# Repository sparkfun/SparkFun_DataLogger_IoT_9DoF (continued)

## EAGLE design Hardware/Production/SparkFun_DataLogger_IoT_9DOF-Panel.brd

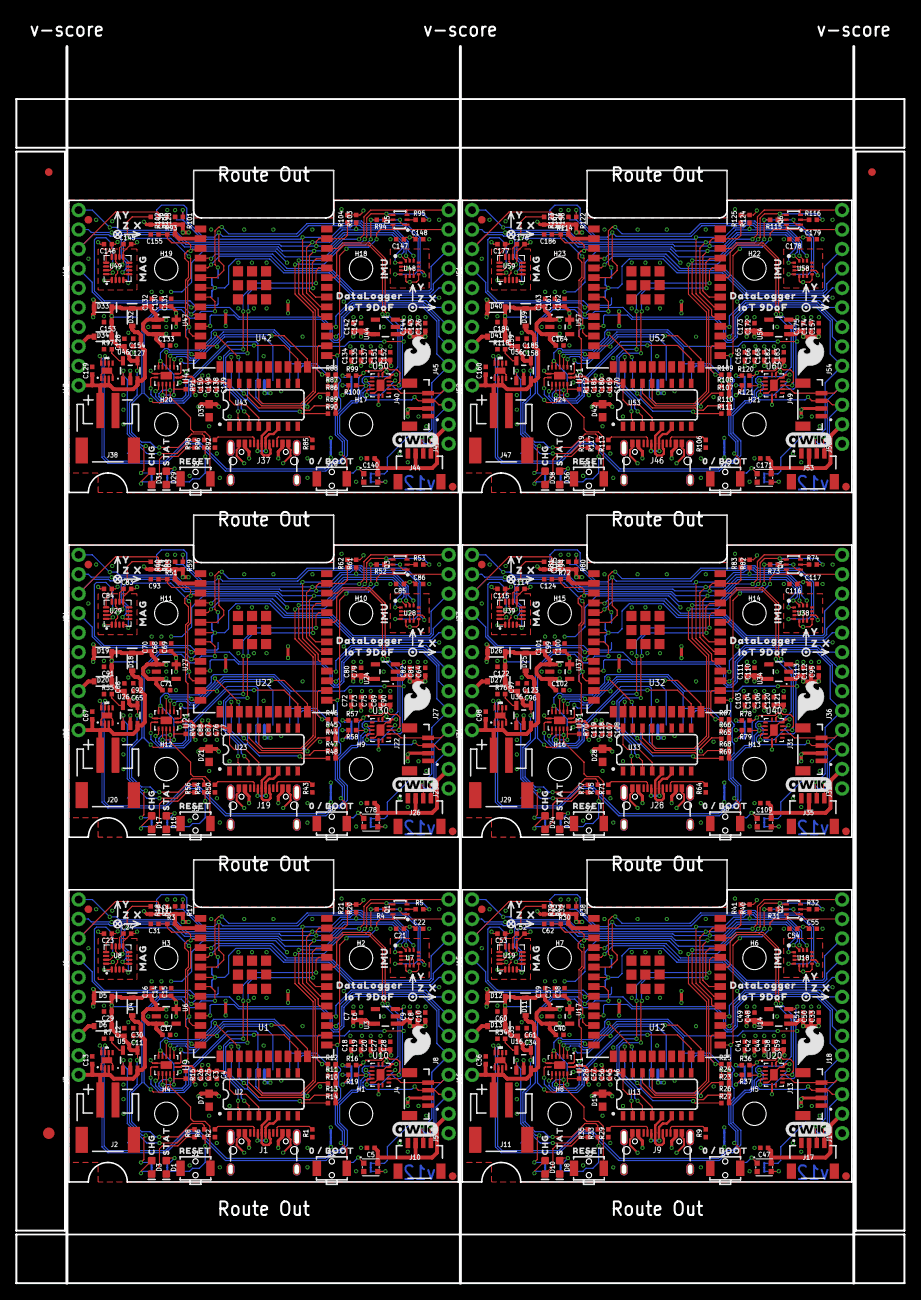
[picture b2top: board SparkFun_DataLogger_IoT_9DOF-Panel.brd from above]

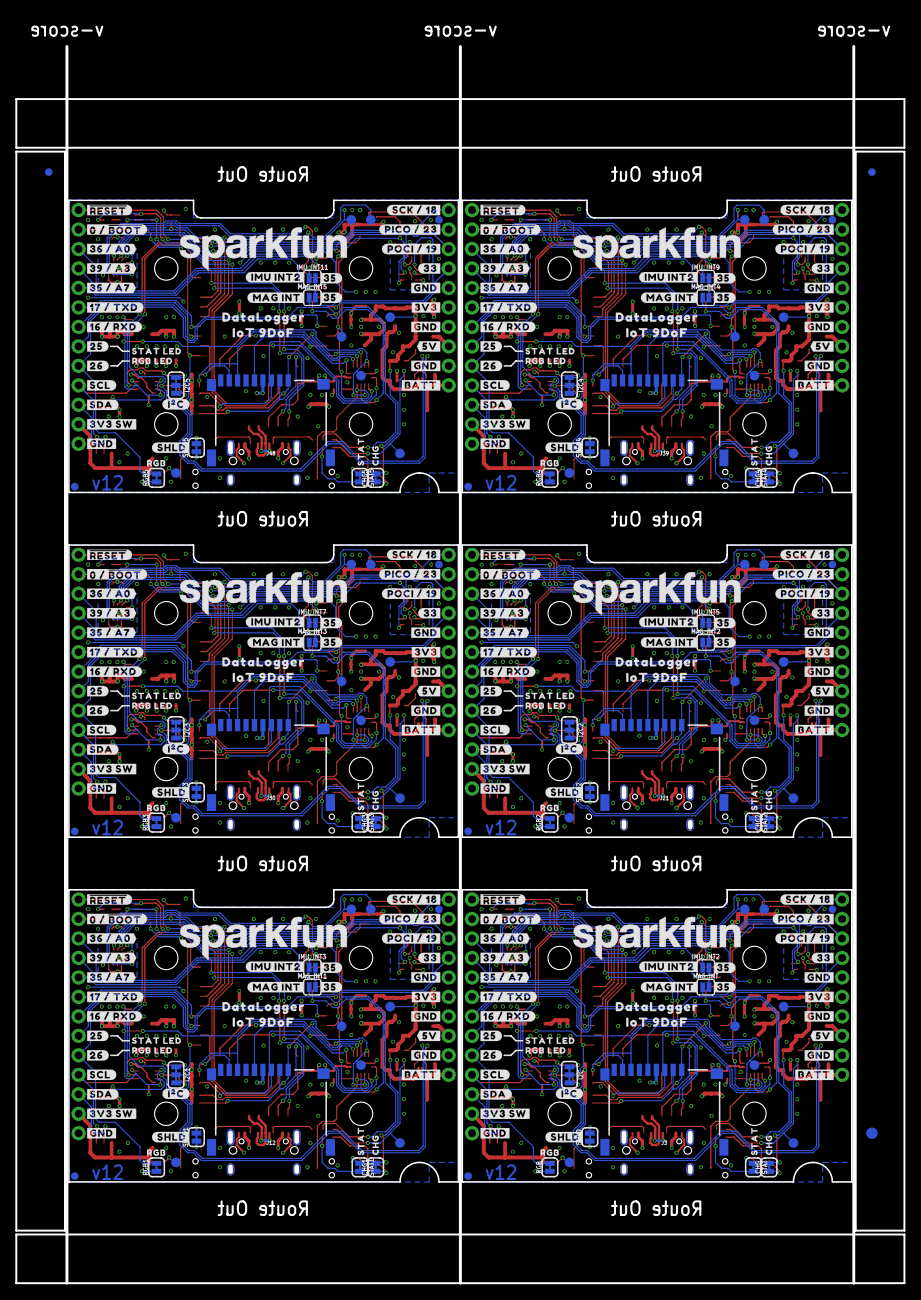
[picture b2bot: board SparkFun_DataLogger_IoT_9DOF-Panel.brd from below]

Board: 4 copper layers, 115.8 x 161.3 mm, 942 parts (327 on the bottom side), 372 nets.

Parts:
C1, C3, C5, C6, C8, C9, C10, C11, C12, C14, C16, C18, C20, C23, C25, C26, C27, C28, C29, C30, C32, C33, C34, C35, C37, C39, C41, C44, C45, C47, C48, C50, C51, C53, C56, C57, C58, C59, C60, C61, C63, C64, C65, C66, C68, C70, C72, C75, C76, C78, C79, C81, C82, C84, C87, C88, C89, C90, C91, C92, C94, C95, C96, C97, C99, C101, C103, C106, C107, C109, C110, C112, C113, C115, C118, C119, C120, C121, C122, C123, C125, C126, C127, C128, C130, C132, C134, C137, C138, C140, C141, C143, C144, C146, C149, C150, C151, C152, C153, C154, C156, C157, C158, C159, C161, C163, C165, C168, C169, C171, C172, C174, C175, C177, C180, C181, C182, C183, C184, C185: 2.2uF; 0402-TIGHT
C2, C7, C13, C15, C17, C19, C21, C22, C36, C38, C40, C42, C43, C49, C54, C55, C67, C69, C71, C73, C74, C80, C85, C86, C98, C100, C102, C104, C105, C111, C116, C117, C129, C131, C133, C135, C136, C142, C147, C148, C160, C162, C164, C166, C167, C173, C178, C179: 0.1uF; 0402-TIGHT
C4, C46, C77, C108, C139, C170: 10nF; 0402-TIGHT
C24, C52, C83, C114, C145, C176: 10uF; 0402-TIGHT
C31, C62, C93, C124, C155, C186: DNP; 0402-TIGHT_NO_CREAM
CHG, CHG1, CHG2, CHG3, CHG4, CHG5: JUMPER-SMT_2_NC_TRACE_SILK; SMT-JUMPER_2_NC_TRACE_SILK
D1, D8, D15, D22, D29, D36: BLUE; LED-0603
D2, D9, D16, D23, D30, D37: WS2812_2020; WS2812-2020
D3, D10, D17, D24, D31, D38: Yellow; LED-0603
D4, D5, D6, D11, D12, D13, D18, D19, D20, D25, D26, D27, D32, D33, D34, D39, D40, D41: 3A/10V/280mV; SOD-323
D7, D14, D21, D28, D35, D42: TVS; 0603
E$1, E$2, E$3, E$4: FIDUCIAL-1X2
E$5, E$6: FIDUCIAL-1.5X3
FD1, FD2, FD3, FD4, FD5, FD6, FD7, FD8, FD9, FD10, FD11, FD12, FD13, FD14, FD15, FD16, FD17, FD18, FD19, FD20, FD21, FD22, FD23, FD24: FIDUCIAL1X2; FIDUCIAL-1X2
H1, H2, H3, H4, H5, H6, H7, H8, H9, H10, H11, H12, H13, H14, H15, H16, H17, H18, H19, H20, H21, H22, H23, H24: STAND-OFFTIGHT; STAND-OFF-TIGHT
I2C, I2C1, I2C2, I2C3, I2C4, I2C5: JUMPER-SMT_3_2-NC_TRACE_SILK; SMT-JUMPER_3_2-NC_TRACE_SILK
IMU_!CS!, IMU_!CS!1, IMU_!CS!2, IMU_!CS!3, IMU_!CS!4, IMU_!CS!5: TEST-POINT3X5; PAD.03X.05
IMU_INT1, IMU_INT4, IMU_INT6, IMU_INT8, IMU_INT10, IMU_INT12: TEST-POINT3X5; PAD.03X.05
IMU_INT2, IMU_INT3, IMU_INT5, IMU_INT7, IMU_INT9, IMU_INT11: JUMPER-SMT_2_NO_SILK; SMT-JUMPER_2_NO_SILK
J1, J9, J19, J28, J37, J46: USB-C-16P_4LAYER-PADS
J2, J11, J20, J29, J38, J47: JST-2-SMD
J3, J12, J21, J30, J39, J48: MICRO-SD-PUSH-PUSH-EXT-PIN; MICROSD-EXTERNALPIN
J4, J13, J22, J31, J40, J49: Vertical Qwiic Connector; JST04_1MM_VERT
J5, J6, J14, J15, J23, J24, J32, J33, J41, J42, J50, J51: 1X04_NO_SILK
J7, J16, J25, J34, J43, J52: 1X06_NO_SILK
J8, J18, J27, J36, J45, J54: 1X09_NO_SILK
J10, J17, J26, J35, J44, J53: QWIIC_RIGHT_ANGLE; JST04_1MM_RA
LOGO1, LOGO3, LOGO7, LOGO10, LOGO13, LOGO16: QWIIC_LOGO_6MM; QWIIC_6MM
LOGO2, LOGO5, LOGO8, LOGO11, LOGO14, LOGO17: SFE_LOGO_NAME.2_INCH; SFE_LOGO_NAME_.2
LOGO4, LOGO6, LOGO9, LOGO12, LOGO15, LOGO18: SFE_LOGO_FLAME.2_INCH; SFE_LOGO_FLAME_.2
MAG_!CS!, MAG_!CS!1, MAG_!CS!2, MAG_!CS!3, MAG_!CS!4, MAG_!CS!5: TEST-POINT3X5; PAD.03X.05
MAG_INT, MAG_INT1, MAG_INT2, MAG_INT3, MAG_INT4, MAG_INT5: JUMPER-SMT_2_NO_SILK; SMT-JUMPER_2_NO_SILK
PWREN, PWREN1, PWREN2, PWREN3, PWREN4, PWREN5: TEST-POINT3X5; PAD.03X.05
Q1, Q2, Q3, Q4, Q5, Q6: SC70-6
R1, R2, R9, R29, R43, R50, R64, R71, R85, R92, R106, R113: 5.1k; 0402-TIGHT
R3, R4, R5, R10, R11, R12, R13, R14, R22, R23, R24, R25, R26, R27, R30, R31, R32, R42, R44, R45, R46, R47, R48, R51, R52, R53, R63, R65, R66, R67, R68, R69, R72, R73, R74, R84, R86, R87, R88, R89, R90, R93, R94, R95, R105, R107, R108, R109, R110, R111, R114, R115, R116, R126: 10k; 0402-TIGHT
R6, R8, R33, R35, R54, R56, R75, R77, R96, R98, R117, R119: 1k; 0402-TIGHT
R7, R34, R55, R76, R97, R118: 2.0K; 0402-TIGHT
R15, R17, R18, R20, R21, R28, R38, R39, R40, R41, R49, R59, R60, R61, R62, R70, R80, R81, R82, R83, R91, R101, R102, R103, R104, R112, R122, R123, R124, R125: 100k; 0402-TIGHT
R16, R19, R36, R37, R57, R58, R78, R79, R99, R100, R120, R121: 2.2k; 0402-TIGHT
RGB, RGB1, RGB2, RGB3, RGB4, RGB5: JUMPER-SMT_2_NC_TRACE_SILK; SMT-JUMPER_2_NC_TRACE_SILK
S1, S3, S5, S7, S9, S11: RESET; TACTILE_SWITCH_SMD_RIGHT_ANGLE
S2, S4, S6, S8, S10, S12: BOOT; TACTILE_SWITCH_SMD_RIGHT_ANGLE
SHLD, SHLD1, SHLD2, SHLD3, SHLD4, SHLD5: JUMPER-SMT_2_NC_TRACE_SILK; SMT-JUMPER_2_NC_TRACE_SILK
STAT, STAT1, STAT2, STAT3, STAT4, STAT5: JUMPER-SMT_2_NC_TRACE_SILK; SMT-JUMPER_2_NC_TRACE_SILK
TP1, TP2, TP3, TP4, TP5, TP6: TEST-POINT3X5; PAD.03X.05
U1, U12, U22, U32, U42, U52: ESP-WROOM-32E; ESP-WROOM-32D-NARROW
U2, U13, U23, U33, U43, U53: CH340C; SO016
U3, U6, U14, U17, U24, U27, U34, U37, U44, U47, U54, U57: XC6222B331MR-G; SOT23-5
U4, U15, U25, U35, U45, U55: MAX17048; DFN-8
U5, U16, U26, U36, U46, U56: MCP73831; SOT23-5
U7, U18, U28, U38, U48, U58: ISM330DHCX; LGA-14L
U8, U19, U29, U39, U49, U59: MMC5983MA_QFN16; LGA-16-3X3MM-4X4PINS
U9, U10, U11, U20, U21, U30, U31, U40, U41, U50, U51, U60: 74HC4066_QUAD_BILATERAL_SWITCH_QFN; 14-QFN
U$1, U$99, U$149, U$199, U$249, U$299: IOT_9DOF0
U$2, U$39, U$101, U$151, U$201, U$251: RESET0
U$3, U$6, U$52, U$55, U$102, U$105, U$152, U$155, U$202, U$205, U$252, U$255: STAT0
U$4, U$5, U$53, U$54, U$103, U$104, U$153, U$154, U$203, U$204, U$253, U$254: CHG0
U$7, U$95, U$145, U$195, U$245, U$295: 0_#_BOOT0
U$8, U$56, U$106, U$156, U$206, U$256: IMU0
U$9, U$57, U$107, U$157, U$207, U$257: MAG0
U$10, U$13, U$58, U$61, U$108, U$111, U$158, U$161, U$208, U$211, U$258, U$261: X0
U$11, U$14, U$59, U$62, U$109, U$112, U$159, U$162, U$209, U$212, U$259, U$262: Y0
U$12, U$15, U$60, U$63, U$110, U$113, U$160, U$163, U$210, U$213, U$260, U$263: Z0
U$16, U$64, U$114, U$164, U$214, U$264: ##RESET##0
U$17, U$65, U$115, U$165, U$215, U$265: #0_#_#BOOT##0
U$18, U$66, U$116, U$166, U$216, U$266: #36_#_A0#0
U$19, U$67, U$117, U$167, U$217, U$267: #39_#_A3#0
U$20, U$68, U$118, U$168, U$218, U$268: #35_#_A7#0
U$21, U$69, U$119, U$169, U$219, U$269: #17_#_TXD#0
U$22, U$70, U$120, U$170, U$220, U$270: #16_#_RXD#0
U$23, U$71, U$121, U$171, U$221, U$271: #25#0
U$24, U$72, U$122, U$172, U$222, U$272: #26#0
U$25, U$73, U$123, U$173, U$223, U$273: #SCL#0
U$26, U$74, U$124, U$174, U$224, U$274: #SDA#0
U$27, U$75, U$125, U$175, U$225, U$275: #3V3_SW#0
U$28, U$76, U$126, U$176, U$226, U$276: #GND#0
U$29, U$30, U$31, U$77, U$78, U$79, U$127, U$128, U$129, U$177, U$178, U$179, U$227, U$228, U$229, U$277, U$278, U$279: #GND#1
U$32, U$80, U$130, U$180, U$230, U$280: #BATT#0
U$33, U$81, U$131, U$181, U$231, U$281: #5V#0
U$34, U$82, U$132, U$182, U$232, U$282: #3V3#0
U$35, U$83, U$133, U$183, U$233, U$283: #33#0
U$36, U$84, U$134, U$184, U$234, U$284: #POCI_#_19#0
U$37, U$85, U$135, U$185, U$235, U$285: #PICO_#_23#0
U$38, U$86, U$136, U$186, U$236, U$286: #SCK_#_18#0
U$40, U$87, U$137, U$187, U$237, U$287: #IMU_INT2#0
U$41, U$88, U$138, U$188, U$238, U$288: #MAG_INT#0
U$42, U$43, U$89, U$90, U$139, U$140, U$189, U$190, U$239, U$240, U$289, U$290: #35#0
U$44, U$100, U$150, U$200, U$250, U$300: IOT_9DOF10
U$45, U$91, U$141, U$191, U$241, U$291: #SHLD#0
U$46, U$92, U$142, U$192, U$242, U$292: #I�C#0
U$47, U$93, U$143, U$193, U$243, U$293: STAT_LED0
U$48, U$94, U$144, U$194, U$244, U$294: RGB_LED0
U$49, U$96, U$146, U$196, U$246, U$296: RGB0
U$50, U$97, U$147, U$197, U$247, U$297: DATALOGGER0
U$51, U$98, U$148, U$198, U$248, U$298: DATALOGGER1
VIN, VIN1, VIN2, VIN3, VIN4, VIN5, VIN6, VIN7, VIN8, VIN9, VIN10, VIN11: TEST-POINT3X5; PAD.03X.05

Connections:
3.3V: C1.1, C2.1, C3.1, C4.1, C14.1, C15.1, C21.1, C22.1, C23.1, C25.1, C26.1, C27.1, C28.1, I2C.2, J7.5, R3.2, R17.2, R18.2, R20.2, R21.2, R22.2, U1.2, U2.4, U2.16, U6.5, U7.P5, U7.P8, U8.2, U8.13, U9.14, U10.14
3.3V1: C32.1, C37.1, C38.1, C43.1, C45.1, C46.1, C53.1, C54.1, C55.1, C56.1, C57.1, C58.1, C59.1, I2C1.2, J16.5, R30.2, R38.2, R39.2, R40.2, R41.2, R42.2, U11.14, U12.2, U13.4, U13.16, U17.5, U18.P5, U18.P8, U19.2, U19.13, U20.14
3.3V2: C63.1, C68.1, C69.1, C74.1, C76.1, C77.1, C84.1, C85.1, C86.1, C87.1, C88.1, C89.1, C90.1, I2C2.2, J25.5, R51.2, R59.2, R60.2, R61.2, R62.2, R63.2, U21.14, U22.2, U23.4, U23.16, U27.5, U28.P5, U28.P8, U29.2, U29.13, U30.14
3.3V3: C94.1, C99.1, C100.1, C105.1, C107.1, C108.1, C115.1, C116.1, C117.1, C118.1, C119.1, C120.1, C121.1, I2C3.2, J34.5, R72.2, R80.2, R81.2, R82.2, R83.2, R84.2, U31.14, U32.2, U33.4, U33.16, U37.5, U38.P5, U38.P8, U39.2, U39.13, U40.14
3.3V4: C125.1, C130.1, C131.1, C136.1, C138.1, C139.1, C146.1, C147.1, C148.1, C149.1, C150.1, C151.1, C152.1, I2C4.2, J43.5, R93.2, R101.2, R102.2, R103.2, R104.2, R105.2, U41.14, U42.2, U43.4, U43.16, U47.5, U48.P5, U48.P8, U49.2, U49.13, U50.14
3.3V5: C156.1, C161.1, C162.1, C167.1, C169.1, C170.1, C177.1, C178.1, C179.1, C180.1, C181.1, C182.1, C183.1, I2C5.2, J52.5, R114.2, R122.2, R123.2, R124.2, R125.2, R126.2, U51.14, U52.2, U53.4, U53.16, U57.5, U58.P5, U58.P8, U59.2, U59.13, U60.14
3.3V_SW: C5.1, C6.1, C7.1, C18.1, C19.1, C20.1, D2.VCC, J3.4, J4.2, J5.2, J10.2, R10.2, R11.2, R12.2, R13.2, R14.2, U3.5
3.3V_SW1: C41.1, C42.1, C44.1, C47.1, C48.1, C49.1, D9.VCC, J12.4, J13.2, J14.2, J17.2, R23.2, R24.2, R25.2, R26.2, R27.2, U14.5
3.3V_SW2: C72.1, C73.1, C75.1, C78.1, C79.1, C80.1, D16.VCC, J21.4, J22.2, J23.2, J26.2, R44.2, R45.2, R46.2, R47.2, R48.2, U24.5
3.3V_SW3: C103.1, C104.1, C106.1, C109.1, C110.1, C111.1, D23.VCC, J30.4, J31.2, J32.2, J35.2, R65.2, R66.2, R67.2, R68.2, R69.2, U34.5
3.3V_SW4: C134.1, C135.1, C137.1, C140.1, C141.1, C142.1, D30.VCC, J39.4, J40.2, J41.2, J44.2, R86.2, R87.2, R88.2, R89.2, R90.2, U44.5
3.3V_SW5: C165.1, C166.1, C168.1, C171.1, C172.1, C173.1, D37.VCC, J48.4, J49.2, J50.2, J53.2, R107.2, R108.2, R109.2, R110.2, R111.2, U54.5
5V: D6.A, J7.3
5V1: D13.A, J16.3
5V2: D20.A, J25.3
5V3: D27.A, J34.3
5V4: D34.A, J43.3
5V5: D41.A, J52.3
!RESET!: C31.1, J8.9, Q1.3, R3.1, S1.2, U1.3, U9.12
!RESET!1: C62.1, J18.9, Q2.3, R30.1, S3.2, U11.12, U12.3
!RESET!2: C93.1, J27.9, Q3.3, R51.1, S5.2, U21.12, U22.3
!RESET!3: C124.1, J36.9, Q4.3, R72.1, S7.2, U31.12, U32.3
!RESET!4: C155.1, J45.9, Q5.3, R93.1, S9.2, U41.12, U42.3
!RESET!5: C186.1, J54.9, Q6.3, R114.1, S11.2, U51.12, U52.3
CAP: C24.1, U8.10
CAP1: C52.1, U19.10
CAP2: C83.1, U29.10
CAP3: C114.1, U39.10
CAP4: C145.1, U49.10
CAP5: C176.1, U59.10
CH340-DTR: Q1.1, R4.2, U2.13
CH340-DTR1: Q2.1, R31.2, U13.13
CH340-DTR2: Q3.1, R52.2, U23.13
CH340-DTR3: Q4.1, R73.2, U33.13
CH340-DTR4: Q5.1, R94.2, U43.13
CH340-DTR5: Q6.1, R115.2, U53.13
CH340-RTS: Q1.4, R5.2, U2.14
CH340-RTS1: Q2.4, R32.2, U13.14
CH340-RTS2: Q3.4, R53.2, U23.14
CH340-RTS3: Q4.4, R74.2, U33.14
CH340-RTS4: Q5.4, R95.2, U43.14
CH340-RTS5: Q6.4, R116.2, U53.14
CH340-RX: U1.35, U2.3
CH340-RX1: U12.35, U13.3
CH340-RX2: U22.35, U23.3
CH340-RX3: U32.35, U33.3
CH340-RX4: U42.35, U43.3
CH340-RX5: U52.35, U53.3
CH340-TX: U1.34, U2.2
CH340-TX1: U12.34, U13.2
CH340-TX2: U22.34, U23.2
CH340-TX3: U32.34, U33.2
CH340-TX4: U42.34, U43.2
CH340-TX5: U52.34, U53.2
D+: J1.A6, J1.B6, U2.5
D+1: J9.A6, J9.B6, U13.5
D+2: J19.A6, J19.B6, U23.5
D+3: J28.A6, J28.B6, U33.5
D+4: J37.A6, J37.B6, U43.5
D+5: J46.A6, J46.B6, U53.5
D-: J1.A7, J1.B7, U2.6
D-1: J9.A7, J9.B7, U13.6
D-2: J19.A7, J19.B7, U23.6
D-3: J28.A7, J28.B7, U33.6
D-4: J37.A7, J37.B7, U43.6
D-5: J46.A7, J46.B7, U53.6
ESP0/!BOOT!: J8.8, Q1.6, S2.2, U1.25
ESP0/!BOOT!1: J18.8, Q2.6, S4.2, U12.25
ESP0/!BOOT!2: J27.8, Q3.6, S6.2, U22.25
ESP0/!BOOT!3: J36.8, Q4.6, S8.2, U32.25
ESP0/!BOOT!4: J45.8, Q5.6, S10.2, U42.25
ESP0/!BOOT!5: J54.8, Q6.6, S12.2, U52.25
ESP1: J15.1, U12.9
ESP2: J24.1, U22.9
ESP2/DAT0: U1.24, U9.1
ESP2/DAT1: U11.1, U12.24
ESP2/DAT2: U21.1, U22.24
ESP2/DAT3: U31.1, U32.24
ESP2/DAT4: U41.1, U42.24
ESP2/DAT5: U51.1, U52.24
ESP3: J33.1, U32.9
ESP4: J42.1, U42.9
ESP4/DAT1: J3.8, R12.1, U1.26
ESP4/DAT2: J12.8, R25.1, U12.26
ESP4/DAT3: J21.8, R46.1, U22.26
ESP4/DAT4: J30.8, R67.1, U32.26
ESP4/DAT5: J39.8, R88.1, U42.26
ESP4/DAT6: J48.8, R109.1, U52.26
ESP5: J51.1, U52.9
ESP5/!IMU_CS!: IMU_!CS!.1, R17.1, U1.29, U7.P12
ESP5/!IMU_CS!1: IMU_!CS!1.1, R38.1, U12.29, U18.P12
ESP5/!IMU_CS!2: IMU_!CS!2.1, R59.1, U22.29, U28.P12
ESP5/!IMU_CS!3: IMU_!CS!3.1, R80.1, U32.29, U38.P12
ESP5/!IMU_CS!4: IMU_!CS!4.1, R101.1, U42.29, U48.P12
ESP5/!IMU_CS!5: IMU_!CS!5.1, R122.1, U52.29, U58.P12
ESP12/DAT1: U11.4, U12.14
ESP12/DAT2: U1.14, U9.4
ESP12/DAT3: U21.4, U22.14
ESP12/DAT4: U31.4, U32.14
ESP12/DAT5: U41.4, U42.14
ESP12/DAT6: U51.4, U52.14
ESP13/DAT1: J12.2, R27.1, U12.16
ESP13/DAT2: J21.2, R48.1, U22.16
ESP13/DAT3: J3.2, R14.1, U1.16
ESP13/DAT4: J30.2, R69.1, U32.16
ESP13/DAT5: J39.2, R90.1, U42.16
ESP13/DAT6: J48.2, R111.1, U52.16
ESP14/CLK: J3.5, U1.13
ESP14/CLK1: J12.5, U12.13
ESP14/CLK2: J21.5, U22.13
ESP14/CLK3: J30.5, U32.13
ESP14/CLK4: J39.5, U42.13
ESP14/CLK5: J48.5, U52.13
ESP15/CMD: U1.23, U9.8
ESP15/CMD1: U11.8, U12.23
ESP15/CMD2: U21.8, U22.23
ESP15/CMD3: U31.8, U32.23
ESP15/CMD4: U41.8, U42.23
ESP15/CMD5: U51.8, U52.23
ESP16/RXD: J8.3, U1.27
ESP16/RXD1: J18.3, U12.27
ESP16/RXD2: J27.3, U22.27
ESP16/RXD3: J36.3, U32.27
ESP16/RXD4: J45.3, U42.27
ESP16/RXD5: J54.3, U52.27
ESP17/TXD: J8.4, U1.28
ESP17/TXD1: J18.4, U12.28
ESP17/TXD2: J27.4, U22.28
ESP17/TXD3: J36.4, U32.28
ESP17/TXD4: J45.4, U42.28
ESP17/TXD5: J54.4, U52.28
ESP18/SCK: J6.4, R20.1, U1.30, U7.P13, U8.1
ESP18/SCK1: J15.4, R40.1, U12.30, U18.P13, U19.1
ESP18/SCK2: J24.4, R61.1, U22.30, U28.P13, U29.1
ESP18/SCK3: J33.4, R82.1, U32.30, U38.P13, U39.1
ESP18/SCK4: J42.4, R103.1, U42.30, U48.P13, U49.1
ESP18/SCK5: J51.4, R124.1, U52.30, U58.P13, U59.1
ESP19/POCI: J6.2, R22.1, U1.31, U7.P1, U8.5
ESP19/POCI1: J15.2, R42.1, U12.31, U18.P1, U19.5
ESP19/POCI2: J24.2, R63.1, U22.31, U28.P1, U29.5
ESP19/POCI3: J33.2, R84.1, U32.31, U38.P1, U39.5
ESP19/POCI4: J42.2, R105.1, U42.31, U48.P1, U49.5
ESP19/POCI5: J51.2, R126.1, U52.31, U58.P1, U59.5
ESP21/SDA: R19.1, U1.33, U4.8, U10.4
ESP21/SDA1: R37.1, U12.33, U15.8, U20.4
ESP21/SDA2: R58.1, U22.33, U25.8, U30.4
ESP21/SDA3: R79.1, U32.33, U35.8, U40.4
ESP21/SDA4: R100.1, U42.33, U45.8, U50.4
ESP21/SDA5: R121.1, U52.33, U55.8, U60.4
ESP22/SCL: R16.2, U1.36, U4.7, U10.11
ESP22/SCL1: R36.2, U12.36, U15.7, U20.11
ESP22/SCL2: R57.2, U22.36, U25.7, U30.11
ESP22/SCL3: R78.2, U32.36, U35.7, U40.11
ESP22/SCL4: R99.2, U42.36, U45.7, U50.11
ESP22/SCL5: R120.2, U52.36, U55.7, U60.11
ESP23/PICO: J6.3, R21.1, U1.37, U7.P14, U8.16
ESP23/PICO1: J15.3, R41.1, U12.37, U18.P14, U19.16
ESP23/PICO2: J24.3, R62.1, U22.37, U28.P14, U29.16
ESP23/PICO3: J33.3, R83.1, U32.37, U38.P14, U39.16
ESP23/PICO4: J42.3, R104.1, U42.37, U48.P14, U49.16
ESP23/PICO5: J51.3, R125.1, U52.37, U58.P14, U59.16
ESP25/LED: J8.2, R6.2, U1.10
ESP25/LED1: J18.2, R33.2, U12.10
ESP25/LED2: J27.2, R54.2, U22.10
ESP25/LED3: J36.2, R75.2, U32.10
ESP25/LED4: J45.2, R96.2, U42.10
ESP25/LED5: J54.2, R117.2, U52.10
ESP26/RGBLED: J8.1, RGB.2, U1.11
ESP26/RGBLED1: J18.1, RGB1.2, U12.11
ESP26/RGBLED2: J27.1, RGB2.2, U22.11
ESP26/RGBLED3: J36.1, RGB3.2, U32.11
ESP26/RGBLED4: J45.1, RGB4.2, U42.11
ESP26/RGBLED5: J54.1, RGB5.2, U52.11
ESP27/!MAG_CS!: MAG_!CS!.1, R18.1, U1.12, U8.4
ESP27/!MAG_CS!1: MAG_!CS!1.1, R39.1, U12.12, U19.4
ESP27/!MAG_CS!2: MAG_!CS!2.1, R60.1, U22.12, U29.4
ESP27/!MAG_CS!3: MAG_!CS!3.1, R81.1, U32.12, U39.4
ESP27/!MAG_CS!4: MAG_!CS!4.1, R102.1, U42.12, U49.4
ESP27/!MAG_CS!5: MAG_!CS!5.1, R123.1, U52.12, U59.4
ESP32/PWREN: U1.8, U9.11
ESP32/PWREN1: U11.11, U12.8
ESP32/PWREN2: U21.11, U22.8
ESP32/PWREN3: U31.11, U32.8
ESP32/PWREN4: U41.11, U42.8
ESP32/PWREN5: U51.11, U52.8
ESP33: J6.1, U1.9
ESP34/IMU_INT1: IMU_INT1.1, U1.6, U7.P4
ESP34/IMU_INT2: IMU_INT4.1, U12.6, U18.P4
ESP34/IMU_INT3: IMU_INT6.1, U22.6, U28.P4
ESP34/IMU_INT4: IMU_INT8.1, U32.6, U38.P4
ESP34/IMU_INT5: IMU_INT10.1, U42.6, U48.P4
ESP34/IMU_INT6: IMU_INT12.1, U52.6, U58.P4
ESP35/A1: IMU_INT3.2, J18.5, MAG_INT1.2, U12.7
ESP35/A2: IMU_INT5.2, J27.5, MAG_INT2.2, U22.7
ESP35/A3: IMU_INT7.2, J36.5, MAG_INT3.2, U32.7
ESP35/A4: IMU_INT9.2, J45.5, MAG_INT4.2, U42.7
ESP35/A5: IMU_INT11.2, J54.5, MAG_INT5.2, U52.7
ESP35/A7: IMU_INT2.2, J8.5, MAG_INT.2, U1.7
ESP36/A0: J8.7, U1.4
ESP36/A1: J18.7, U12.4
ESP36/A2: J27.7, U22.4
ESP36/A3: J36.7, U32.4
ESP36/A4: J45.7, U42.4
ESP36/A5: J54.7, U52.4
ESP39/A1: J18.6, U12.5
ESP39/A2: J27.6, U22.5
ESP39/A3: J8.6, U1.5
ESP39/A4: J36.6, U32.5
ESP39/A5: J45.6, U42.5
ESP39/A6: J54.6, U52.5
GND: C1.2, C2.2, C3.2, C4.2, C5.2, C6.2, C7.2, C8.2, C9.2, C10.2, C11.2, C12.2, C13.2, C14.2, C15.2, C16.2, C17.2, C18.2, C19.2, C20.2, C21.2, C22.2, C23.2, C24.2, C25.2, C26.2, C27.2, C28.2, C29.2, C30.2, C31.2, D1.C, D2.GND, D7.1, J1.GND, J1.GND2, J2.1, J3.6, J3.10, J3.11, J3.12, J3.13, J4.1, J5.1, J7.2, J7.4, J7.6, J10.1, R1.1, R2.1, R7.1, R15.1, S1.1, S2.1, SHLD.1, U1.1, U1.15, U1.38, U1.GND1, U1.GNDT1, U1.GNDT2, U1.GNDT3, U1.GNDT4, U1.GNDT5, U1.GNDT6, U1.GNDT7, U1.GNDT8, U2.1, U3.2, U4.1, U4.4, U4.6, U4.9, U5.2, U6.2, U7.P2, U7.P3, U7.P6, U7.P7, U8.9, U8.11, U9.7, U9.EPAD, U10.6, U10.7, U10.13, U10.EPAD
GND1: C32.2, C33.2, C34.2, C35.2, C36.2, C37.2, C38.2, C39.2, C40.2, C41.2, C42.2, C43.2, C44.2, C45.2, C46.2, C47.2, C48.2, C49.2, C50.2, C51.2, C52.2, C53.2, C54.2, C55.2, C56.2, C57.2, C58.2, C59.2, C60.2, C61.2, C62.2, D8.C, D9.GND, D14.1, J9.GND, J9.GND2, J11.1, J12.6, J12.10, J12.11, J12.12, J12.13, J13.1, J14.1, J16.2, J16.4, J16.6, J17.1, R9.1, R28.1, R29.1, R34.1, S3.1, S4.1, SHLD1.1, U11.7, U11.EPAD, U12.1, U12.15, U12.38, U12.GND1, U12.GNDT1, U12.GNDT2, U12.GNDT3, U12.GNDT4, U12.GNDT5, U12.GNDT6, U12.GNDT7, U12.GNDT8, U13.1, U14.2, U15.1, U15.4, U15.6, U15.9, U16.2, U17.2, U18.P2, U18.P3, U18.P6, U18.P7, U19.9, U19.11, U20.6, U20.7, U20.13, U20.EPAD
GND2: C63.2, C64.2, C65.2, C66.2, C67.2, C68.2, C69.2, C70.2, C71.2, C72.2, C73.2, C74.2, C75.2, C76.2, C77.2, C78.2, C79.2, C80.2, C81.2, C82.2, C83.2, C84.2, C85.2, C86.2, C87.2, C88.2, C89.2, C90.2, C91.2, C92.2, C93.2, D15.C, D16.GND, D21.1, J19.GND, J19.GND2, J20.1, J21.6, J21.10, J21.11, J21.12, J21.13, J22.1, J23.1, J25.2, J25.4, J25.6, J26.1, R43.1, R49.1, R50.1, R55.1, S5.1, S6.1, SHLD2.1, U21.7, U21.EPAD, U22.1, U22.15, U22.38, U22.GND1, U22.GNDT1, U22.GNDT2, U22.GNDT3, U22.GNDT4, U22.GNDT5, U22.GNDT6, U22.GNDT7, U22.GNDT8, U23.1, U24.2, U25.1, U25.4, U25.6, U25.9, U26.2, U27.2, U28.P2, U28.P3, U28.P6, U28.P7, U29.9, U29.11, U30.6, U30.7, U30.13, U30.EPAD
GND3: C94.2, C95.2, C96.2, C97.2, C98.2, C99.2, C100.2, C101.2, C102.2, C103.2, C104.2, C105.2, C106.2, C107.2, C108.2, C109.2, C110.2, C111.2, C112.2, C113.2, C114.2, C115.2, C116.2, C117.2, C118.2, C119.2, C120.2, C121.2, C122.2, C123.2, C124.2, D22.C, D23.GND, D28.1, J28.GND, J28.GND2, J29.1, J30.6, J30.10, J30.11, J30.12, J30.13, J31.1, J32.1, J34.2, J34.4, J34.6, J35.1, R64.1, R70.1, R71.1, R76.1, S7.1, S8.1, SHLD3.1, U31.7, U31.EPAD, U32.1, U32.15, U32.38, U32.GND1, U32.GNDT1, U32.GNDT2, U32.GNDT3, U32.GNDT4, U32.GNDT5, U32.GNDT6, U32.GNDT7, U32.GNDT8, U33.1, U34.2, U35.1, U35.4, U35.6, U35.9, U36.2, U37.2, U38.P2, U38.P3, U38.P6, U38.P7, U39.9, U39.11, U40.6, U40.7, U40.13, U40.EPAD
GND4: C125.2, C126.2, C127.2, C128.2, C129.2, C130.2, C131.2, C132.2, C133.2, C134.2, C135.2, C136.2, C137.2, C138.2, C139.2, C140.2, C141.2, C142.2, C143.2, C144.2, C145.2, C146.2, C147.2, C148.2, C149.2, C150.2, C151.2, C152.2, C153.2, C154.2, C155.2, D29.C, D30.GND, D35.1, J37.GND, J37.GND2, J38.1, J39.6, J39.10, J39.11, J39.12, J39.13, J40.1, J41.1, J43.2, J43.4, J43.6, J44.1, R85.1, R91.1, R92.1, R97.1, S9.1, S10.1, SHLD4.1, U41.7, U41.EPAD, U42.1, U42.15, U42.38, U42.GND1, U42.GNDT1, U42.GNDT2, U42.GNDT3, U42.GNDT4, U42.GNDT5, U42.GNDT6, U42.GNDT7, U42.GNDT8, U43.1, U44.2, U45.1, U45.4, U45.6, U45.9, U46.2, U47.2, U48.P2, U48.P3, U48.P6, U48.P7, U49.9, U49.11, U50.6, U50.7, U50.13, U50.EPAD
GND5: C156.2, C157.2, C158.2, C159.2, C160.2, C161.2, C162.2, C163.2, C164.2, C165.2, C166.2, C167.2, C168.2, C169.2, C170.2, C171.2, C172.2, C173.2, C174.2, C175.2, C176.2, C177.2, C178.2, C179.2, C180.2, C181.2, C182.2, C183.2, C184.2, C185.2, C186.2, D36.C, D37.GND, D42.1, J46.GND, J46.GND2, J47.1, J48.6, J48.10, J48.11, J48.12, J48.13, J49.1, J50.1, J52.2, J52.4, J52.6, J53.1, R106.1, R112.1, R113.1, R118.1, S11.1, S12.1, SHLD5.1, U51.7, U51.EPAD, U52.1, U52.15, U52.38, U52.GND1, U52.GNDT1, U52.GNDT2, U52.GNDT3, U52.GNDT4, U52.GNDT5, U52.GNDT6, U52.GNDT7, U52.GNDT8, U53.1, U54.2, U55.1, U55.4, U55.6, U55.9, U56.2, U57.2, U58.P2, U58.P3, U58.P6, U58.P7, U59.9, U59.11, U60.6, U60.7, U60.13, U60.EPAD
IMU_INT1: IMU_INT3.1, U18.P9
IMU_INT2: IMU_INT2.1, U7.P9
IMU_INT3: IMU_INT5.1, U28.P9
IMU_INT4: IMU_INT7.1, U38.P9
IMU_INT5: IMU_INT9.1, U48.P9
IMU_INT6: IMU_INT11.1, U58.P9
MAG_INT: MAG_INT.1, U8.15
MAG_INT1: MAG_INT1.1, U19.15
MAG_INT2: MAG_INT2.1, U29.15
MAG_INT3: MAG_INT3.1, U39.15
MAG_INT4: MAG_INT4.1, U49.15
MAG_INT5: MAG_INT5.1, U59.15
unnamed: J1.B5, R1.2
unnamed: J1.A5, R2.2
unnamed: J9.B5, R9.2
unnamed: Q1.2, R5.1
unnamed: Q1.5, R4.1
unnamed: R6.1, STAT.2
unnamed: D2.DO, TP1.1
unnamed: CHG.1, D3.A
unnamed: D3.C, R8.1
unnamed: R8.2, U5.1, VIN1.1
unnamed: R7.2, U5.5
unnamed: D2.DI, RGB.1
unnamed: D1.A, STAT.1
unnamed: J9.A5, R29.2
unnamed: Q2.2, R32.1
unnamed: I2C.1, R16.1
unnamed: I2C.3, R19.2
unnamed: Q2.5, R31.1
unnamed: D9.DO, TP2.1
unnamed: R34.2, U16.5
unnamed: R33.1, STAT1.2
unnamed: D8.A, STAT1.1
unnamed: I2C1.1, R36.1
unnamed: I2C1.3, R37.2
unnamed: CHG1.1, D10.A
unnamed: D10.C, R35.1
unnamed: R35.2, U16.1, VIN3.1
unnamed: D9.DI, RGB1.1
unnamed: J19.B5, R43.2
unnamed: J19.A5, R50.2
unnamed: Q3.2, R53.1
unnamed: Q3.5, R52.1
unnamed: D16.DO, TP3.1
unnamed: R55.2, U26.5
unnamed: R54.1, STAT2.2
unnamed: D15.A, STAT2.1
unnamed: I2C2.1, R57.1
unnamed: I2C2.3, R58.2
unnamed: CHG2.1, D17.A
unnamed: D17.C, R56.1
unnamed: R56.2, U26.1, VIN5.1
unnamed: D16.DI, RGB2.1
unnamed: J28.B5, R64.2
unnamed: J28.A5, R71.2
unnamed: Q4.2, R74.1
unnamed: Q4.5, R73.1
unnamed: D23.DO, TP4.1
unnamed: R76.2, U36.5
unnamed: R75.1, STAT3.2
unnamed: D22.A, STAT3.1
unnamed: I2C3.1, R78.1
unnamed: I2C3.3, R79.2
unnamed: CHG3.1, D24.A
unnamed: D24.C, R77.1
unnamed: R77.2, U36.1, VIN7.1
unnamed: D23.DI, RGB3.1
unnamed: J37.B5, R85.2
unnamed: J37.A5, R92.2
unnamed: Q5.2, R95.1
unnamed: Q5.5, R94.1
unnamed: D30.DO, TP5.1
unnamed: R97.2, U46.5
unnamed: R96.1, STAT4.2
unnamed: D29.A, STAT4.1
unnamed: I2C4.1, R99.1
unnamed: I2C4.3, R100.2
unnamed: CHG4.1, D31.A
unnamed: D31.C, R98.1
unnamed: R98.2, U46.1, VIN9.1
unnamed: D30.DI, RGB4.1
unnamed: J46.B5, R106.2
unnamed: J46.A5, R113.2
unnamed: Q6.2, R116.1
unnamed: Q6.5, R115.1
unnamed: D37.DO, TP6.1
unnamed: R118.2, U56.5
unnamed: R117.1, STAT5.2
unnamed: D36.A, STAT5.1
unnamed: I2C5.1, R120.1
unnamed: I2C5.3, R121.2
unnamed: CHG5.1, D38.A
unnamed: D38.C, R119.1
unnamed: R119.2, U56.1, VIN11.1
unnamed: D37.DI, RGB5.1
PWREN: PWREN.1, R15.2, U3.3, U9.5, U9.6, U9.10, U9.13, U10.5, U10.12
PWREN1: PWREN1.1, R28.2, U11.5, U11.6, U11.10, U11.13, U14.3, U20.5, U20.12
PWREN2: PWREN2.1, R49.2, U21.5, U21.6, U21.10, U21.13, U24.3, U30.5, U30.12
PWREN3: PWREN3.1, R70.2, U31.5, U31.6, U31.10, U31.13, U34.3, U40.5, U40.12
PWREN4: PWREN4.1, R91.2, U41.5, U41.6, U41.10, U41.13, U44.3, U50.5, U50.12
PWREN5: PWREN5.1, R112.2, U51.5, U51.6, U51.10, U51.13, U54.3, U60.5, U60.12
QWIIC_SCL: J4.4, J5.4, J10.4, U10.10
QWIIC_SCL1: J13.4, J14.4, J17.4, U20.10
QWIIC_SCL2: J22.4, J23.4, J26.4, U30.10
QWIIC_SCL3: J31.4, J32.4, J35.4, U40.10
QWIIC_SCL4: J40.4, J41.4, J44.4, U50.10
QWIIC_SCL5: J49.4, J50.4, J53.4, U60.10
QWIIC_SDA: J4.3, J5.3, J10.3, U10.3
QWIIC_SDA1: J13.3, J14.3, J17.3, U20.3
QWIIC_SDA2: J22.3, J23.3, J26.3, U30.3
QWIIC_SDA3: J31.3, J32.3, J35.3, U40.3
QWIIC_SDA4: J40.3, J41.3, J44.3, U50.3
QWIIC_SDA5: J49.3, J50.3, J53.3, U60.3
SD_CMD: J3.3, R10.1, U9.9
SD_CMD1: J12.3, R23.1, U11.9
SD_CMD2: J21.3, R44.1, U21.9
SD_CMD3: J30.3, R65.1, U31.9
SD_CMD4: J39.3, R86.1, U41.9
SD_CMD5: J48.3, R107.1, U51.9
SD_DAT0: J3.7, R11.1, U9.2
SD_DAT1: J12.7, R24.1, U11.2
SD_DAT2: J3.1, R13.1, U9.3
SD_DAT3: J12.1, R26.1, U11.3
SD_DAT4: J21.7, R45.1, U21.2
SD_DAT5: J21.1, R47.1, U21.3
SD_DAT6: J30.7, R66.1, U31.2
SD_DAT7: J30.1, R68.1, U31.3
SD_DAT8: J39.7, R87.1, U41.2
SD_DAT9: J39.1, R89.1, U41.3
SD_DAT10: J48.7, R108.1, U51.2
SD_DAT11: J48.1, R110.1, U51.3
SHIELD: J1.SHLD1, J1.SHLD2, J1.SHLD3, J1.SHLD4, SHLD.2
SHIELD1: J9.SHLD1, J9.SHLD2, J9.SHLD3, J9.SHLD4, SHLD1.2
SHIELD2: J19.SHLD1, J19.SHLD2, J19.SHLD3, J19.SHLD4, SHLD2.2
SHIELD3: J28.SHLD1, J28.SHLD2, J28.SHLD3, J28.SHLD4, SHLD3.2
SHIELD4: J37.SHLD1, J37.SHLD2, J37.SHLD3, J37.SHLD4, SHLD4.2
SHIELD5: J46.SHLD1, J46.SHLD2, J46.SHLD3, J46.SHLD4, SHLD5.2
VIN: C8.1, C9.1, C10.1, C12.1, C16.1, C17.1, C29.1, CHG.2, D4.C, D5.C, D6.C, U3.1, U5.4, U6.1, U6.3, VIN.1
VIN1: C33.1, C35.1, C39.1, C40.1, C50.1, C51.1, C60.1, CHG1.2, D11.C, D12.C, D13.C, U14.1, U16.4, U17.1, U17.3, VIN2.1
VIN2: C64.1, C66.1, C70.1, C71.1, C81.1, C82.1, C91.1, CHG2.2, D18.C, D19.C, D20.C, U24.1, U26.4, U27.1, U27.3, VIN4.1
VIN3: C95.1, C97.1, C101.1, C102.1, C112.1, C113.1, C122.1, CHG3.2, D25.C, D26.C, D27.C, U34.1, U36.4, U37.1, U37.3, VIN6.1
VIN4: C126.1, C128.1, C132.1, C133.1, C143.1, C144.1, C153.1, CHG4.2, D32.C, D33.C, D34.C, U44.1, U46.4, U47.1, U47.3, VIN8.1
VIN5: C157.1, C159.1, C163.1, C164.1, C174.1, C175.1, C184.1, CHG5.2, D39.C, D40.C, D41.C, U54.1, U56.4, U57.1, U57.3, VIN10.1
V_BATT: C11.1, C13.1, C30.1, D4.A, J2.2, J7.1, U4.2, U4.3, U5.3
V_BATT1: C34.1, C36.1, C61.1, D11.A, J11.2, J16.1, U15.2, U15.3, U16.3
V_BATT2: C65.1, C67.1, C92.1, D18.A, J20.2, J25.1, U25.2, U25.3, U26.3
V_BATT3: C96.1, C98.1, C123.1, D25.A, J29.2, J34.1, U35.2, U35.3, U36.3
V_BATT4: C127.1, C129.1, C154.1, D32.A, J38.2, J43.1, U45.2, U45.3, U46.3
V_BATT5: C158.1, C160.1, C185.1, D39.A, J47.2, J52.1, U55.2, U55.3, U56.3
V_USB: D5.A, D7.2, J1.VBUS1, J1.VBUS2
V_USB1: D12.A, D14.2, J9.VBUS1, J9.VBUS2
V_USB2: D19.A, D21.2, J19.VBUS1, J19.VBUS2
V_USB3: D26.A, D28.2, J28.VBUS1, J28.VBUS2
V_USB4: D33.A, D35.2, J37.VBUS1, J37.VBUS2
V_USB5: D40.A, D42.2, J46.VBUS1, J46.VBUS2

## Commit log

2022-09-12 v10 PCB with examples
2023-02-06 v11 - SparkFun_DataLogger_IoT_9DOF
2023-05-19 Add test sketch warning
2023-05-19 Add a warning to the test sketches
2023-09-06 Update references product name
2024-04-23 Push silk changes.
2024-04-23 Push updated changes to new rev.
